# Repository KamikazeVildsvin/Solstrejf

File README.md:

# Solstrejf - 4 Voice Sine Wave Drone Oscillator
This repository contains the simulation, schematic ,and PCB files for **Solstrejf**.
Some custom KiCad footprints, 3D models, and symbols are used in this project. 
This is included as a git submodule, which means that if you want to work with the KiCad projects in this repo, it should be cloned with the `--recursive` option like so: 

```
git clone --recursive "https://github.com/KamikazeVildsvin/Solstrejf.git"
```

### Introduction & Overview
Solstrejf, roughly translated from Danish to "sun streak" or "sun touch", is a four-voice analog sine wave drone oscillator. 
I was on a hike in Sweden out near a beautiful forest lake just around the break of dawn. 
The way the sun interacted with nature gave me a real sense of calm and ease. 
At that moment I thought, what if I could create an instrument that would be able to replicate this feeling? 
A sine wave drone synthesizer came to my mind, similar to the early Musique Concrète test equipment techniques.

###### Block Diagram

I wanted the instrument to be playful and interactive. 
Four sine wave oscillators in itself are maybe not that interesting and can become static. 
A modulation matrix, which would allow for all four voices to modulate parameters like frequency and amplitude on all other voices would create more complex soundscapes. 
The basic idea and block diagram can be seen above, where four identical voice boards are connected to the mod-matrix board and a power supply/mixer board for output summation.

###### Modulation Matrix & Voice Control Interface

The image above is a render of the modulation matrix and four of the voice board control front panels.
This is essentially user interface of the synthesizer.

## PCB's - KiCad Projects
As indicated by the block diagram above, Solstrejf is broken into four different sub-blocks and PCB's:

- A Power Supply Unit (PSU) & Mixer PCB
- A Modulation Matrix PCB
- A Voice board PCB (x4)
- A Voice board Front Panel PCB (x4)

Each of these PCB's have their own KiCad project with an associated schematic. 
The [`schematics`](schematics) directory contains some of the latest prints of the different schematics. 
The revision may not match with the KiCad files, so be sure to double check the actual KiCad project files to be certain.

#### Interactive BOM
All of the four PCB's have an interactive BOM which is generated using the [InteractiveHtmlBom](https://github.com/openscopeproject/InteractiveHtmlBom) KiCad plugin.
The interactive bom allows to see where the components should be placed on the board and also have a checklist build in, which makes it much easier to assemble the PCB's.
You can also export the BOM to a CSV or TXT file for a more traditional BOM.

### PSU / Audio Mixer
Use to generate the +/-15V supply and sum all of the left and right audio channels of the four voices.

[KiCad Project Files](pcb/solstrejf-PSU-mixer/)

[Link to interactive BOM](https://html-preview.github.io/?url=https://github.com/KamikazeVildsvin/Solstrejf/blob/master/pcb/solstrejf-PSU-mixer/bom/ibom.html)

###### PCB

###### 3D Model : Top View

###### 3D Model : Side View

### Mod-Matrix
Connects to each of the four voice boards to route the modulation from and to each of the voices.
Each voice can modulate the amplitude, frequency and pan of all other voices.

[KiCad Project Files](pcb/solstrejf-modmatrix-pots)

[Link to interactive BOM](https://html-preview.github.io/?url=https://github.com/KamikazeVildsvin/Solstrejf/blob/master/pcb/solstrejf-modmatrix-pots/bom/ibom.html)

###### PCB 

###### 3D Model : Front-Side

###### 3D Model : Back-Side 

### Voice board 
The voice board is the actual sine wave oscillator and control voltage board.
Solstrejf consists of four of these voice boards.

[KiCad Project Files](pcb/solstrejf-voiceboard-core/)

[Link to interactive BOM](https://html-preview.github.io/?url=https://github.com/KamikazeVildsvin/Solstrejf/blob/master/pcb/solstrejf-voiceboard-core/bom/ibom.html)

###### PCB

###### 3D Model : Top View

###### 3D Model : Side View

### Voice board Front Panel
The voice board needs a control interface for the base pan, frequency, and volume. All of the potentiometers that control the voice board are located on this front panel for easier assembling. 

[KiCad Project Files](pcb/solstrejf-voiceboard-frontpanel/)

[Link to interactive BOM](https://html-preview.github.io/?url=https://github.com/KamikazeVildsvin/Solstrejf/blob/master/pcb/solstrejf-voiceboard-frontpanel/bom/ibom.html)

###### PCB 

###### 3D Model : Front Side

###### 3D Model : Back Side 

# Prototype Sponsorship - PCBWay
[PCBway](https://www.pcbway.com/) was so kind to reach out and offer to sponsor the first batch of all four PCBs for Solstrejf!
Essentially, they paid for the production of 5x of each of the four PCBs, which was a great help to reduce the cost of this project.

It was very easy to order from PCBWay using the [PCBWay KiCad Export Plugin](https://github.com/pcbway/PCBWay-Plug-in-for-Kicad).
With one click, all of the needed Gerber and drill files were created and packaged in a neat zip file that could be uploaded directly to PCBWay's website for ordering.

I'm very satisfied with the build quality of the PCBs that I have received for my first prototype of Solstrejf.
The silkscreen and edge cuts were very smooth and pleasant to look at, which especially is nice for the modulation matrix and the voice board front panels (since the user has to look at these PCBs).

Thanks to PCBWay for sponsoring the prototype PCBs.

*pictures coming soon...*

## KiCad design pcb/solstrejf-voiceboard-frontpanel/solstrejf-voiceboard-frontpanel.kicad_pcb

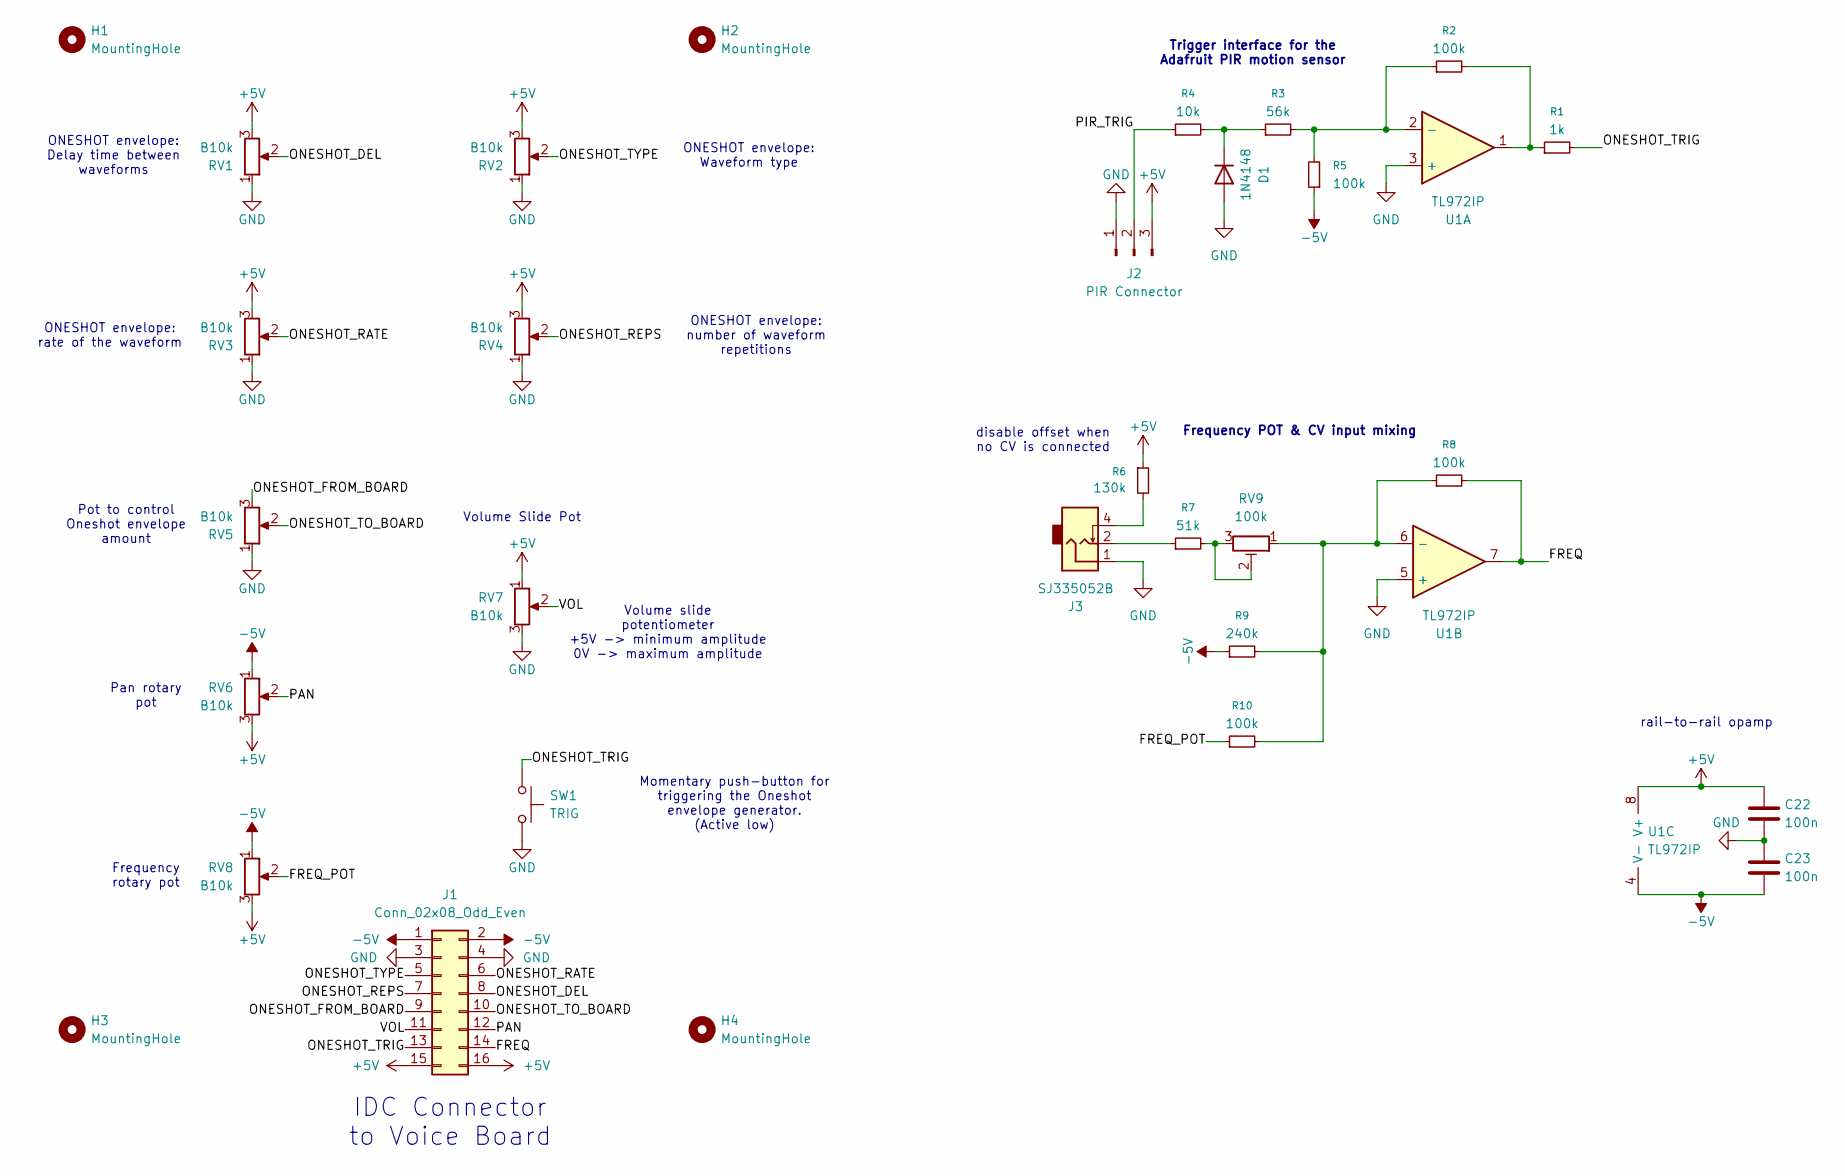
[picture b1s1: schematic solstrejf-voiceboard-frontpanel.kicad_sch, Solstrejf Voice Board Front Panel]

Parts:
C22, C23: 100n; C_Disc_D5.0mm_W2.5mm_P5.00mm
D1: 1N4148; D_DO-35_SOD27_P7.62mm_Horizontal
H1, H2, H3, H4: MountingHole; MountingHole_3.2mm_M3_DIN965
J1: Conn_02x08_Odd_Even; IDC-Header_2x08_P2.54mm_Vertical
J2: PIR Connector; PinHeader_1x03_P2.54mm_Vertical
J3: SJ335052B
R1: 1k; R_Axial_DIN0207_L6.3mm_D2.5mm_P10.16mm_Horizontal
R2, R5, R8, R10: 100k; R_Axial_DIN0207_L6.3mm_D2.5mm_P10.16mm_Horizontal
R3: 56k; R_Axial_DIN0207_L6.3mm_D2.5mm_P10.16mm_Horizontal
R4: 10k; R_Axial_DIN0207_L6.3mm_D2.5mm_P10.16mm_Horizontal
R6: 130k; R_Axial_DIN0207_L6.3mm_D2.5mm_P10.16mm_Horizontal
R7: 51k; R_Axial_DIN0207_L6.3mm_D2.5mm_P10.16mm_Horizontal
R9: 240k; R_Axial_DIN0207_L6.3mm_D2.5mm_P10.16mm_Horizontal
RV1, RV2, RV3, RV4, RV5, RV6, RV8: B10k; Potentiometer_Alpha_RD901F-40-00D_Single_Vertical
RV7: B10k; Potentiometer_Alpha_slide_pot_30mm
RV9: 100k; Potentiometer_Bourns_3296Y_Vertical
SW1: TRIG; SW_SPST_Omron_B3F-40xx
U1: TL972IP; DIP-8_W7.62mm_Socket

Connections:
+5V: C22.1, J1.15, J1.16, J2.3, R6.1, RV1.3, RV2.3, RV3.3, RV4.3, RV6.3, RV7.1, RV8.3, U1.8 (V+)
-5V: C23.2, J1.1, J1.2, R5.1, R9.1, RV6.1, RV8.1, U1.4 (V-)
/FREQ: J1.14, R8.2, U1.7
/FREQ_POT: R10.1, RV8.2
/ONESHOT_DEL: J1.8, RV1.2
/ONESHOT_FROM_BOARD: J1.9, RV5.3
/ONESHOT_RATE: J1.6, RV3.2
/ONESHOT_REPS: J1.7, RV4.2
/ONESHOT_TO_BOARD: J1.10, RV5.2
/ONESHOT_TRIG: J1.13, R1.2, SW1.1
/ONESHOT_TYPE: J1.5, RV2.2
/PAN: J1.12, RV6.2
/PIR_TRIG: J2.2, R4.1
/VOL: J1.11, RV7.2
GND: C22.2, C23.1, D1.2 (A), J1.3, J1.4, J2.1, J3.1, RV1.1, RV2.1, RV3.1, RV4.1, RV5.1, RV7.3, SW1.2, U1.3 (+), U1.5 (+)
unnamed: D1.1 (K), R3.1, R4.2
unnamed: J3.2, R7.1
unnamed: J3.4, R6.2
unnamed: R1.1, R2.2, U1.1
unnamed: R7.2, RV9.2, RV9.3
unnamed: R2.1, R3.2, R5.2, U1.2 (-)
unnamed: R8.1, R9.2, R10.2, RV9.1, U1.6 (-)

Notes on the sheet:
Pan rotary pot
Trigger interface for the Adafruit PIR motion sensor
ONESHOT envelope: rate of the waveform
disable offset when no CV is connected
Frequency rotary pot
Frequency POT & CV input mixing
Volume slide potentiometer +5V -> minimum amplitude 0V -> maximum amplitude
ONESHOT envelope: number of waveform repetitions
rail-to-rail opamp
IDC Connector to Voice Board
ONESHOT envelope: Waveform type
ONESHOT envelope: Delay time between waveforms
Volume Slide Pot
Pot to control Oneshot envelope amount
Momentary push-button for triggering the Oneshot envelope generator. (Active low)

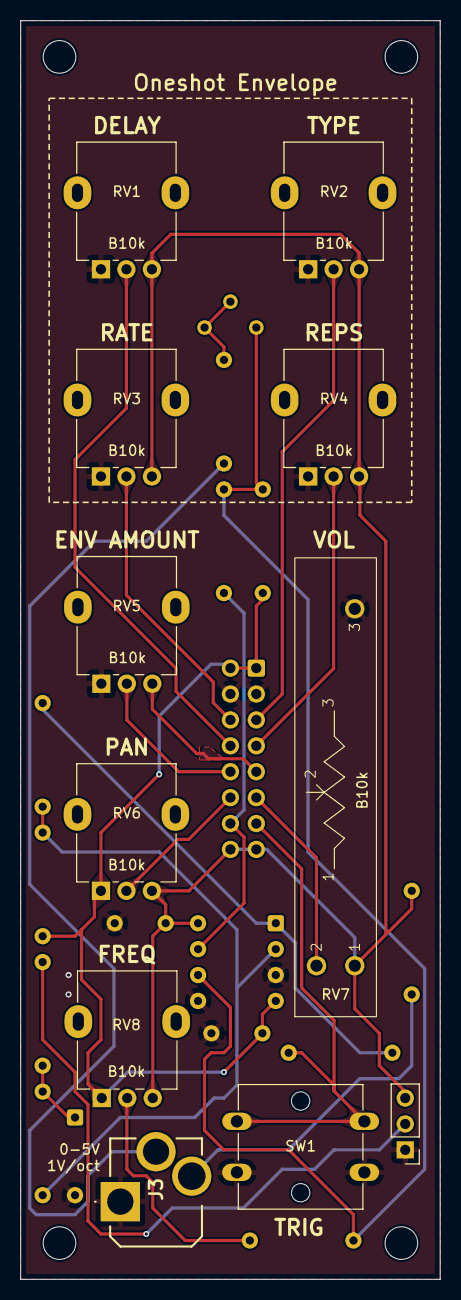
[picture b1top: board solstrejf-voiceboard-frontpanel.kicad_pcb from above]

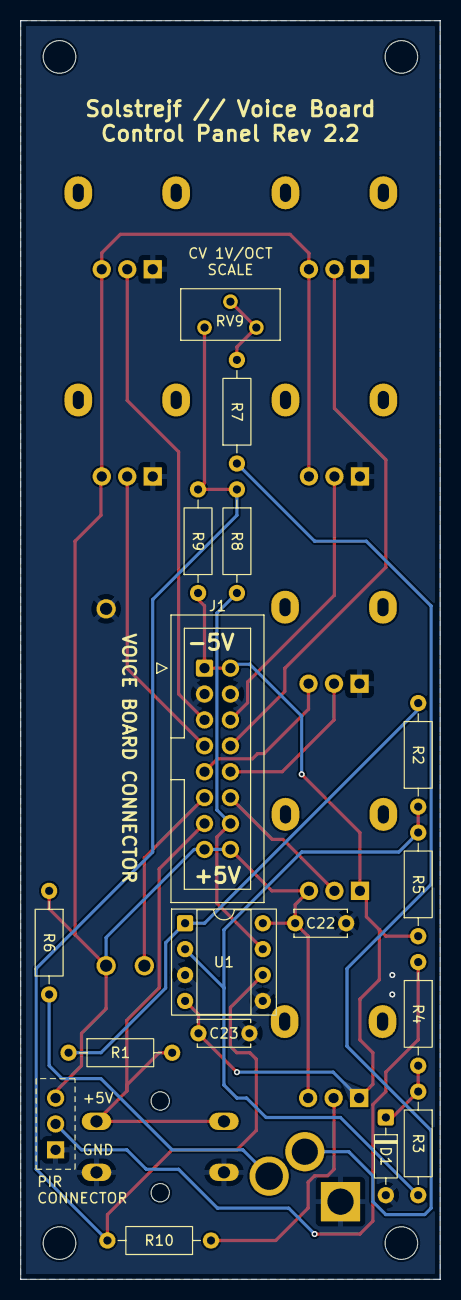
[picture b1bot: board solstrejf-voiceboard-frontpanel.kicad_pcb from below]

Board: 2 copper layers, 41.1 x 123.4 mm, 31 parts (16 on the bottom side), 22 nets.

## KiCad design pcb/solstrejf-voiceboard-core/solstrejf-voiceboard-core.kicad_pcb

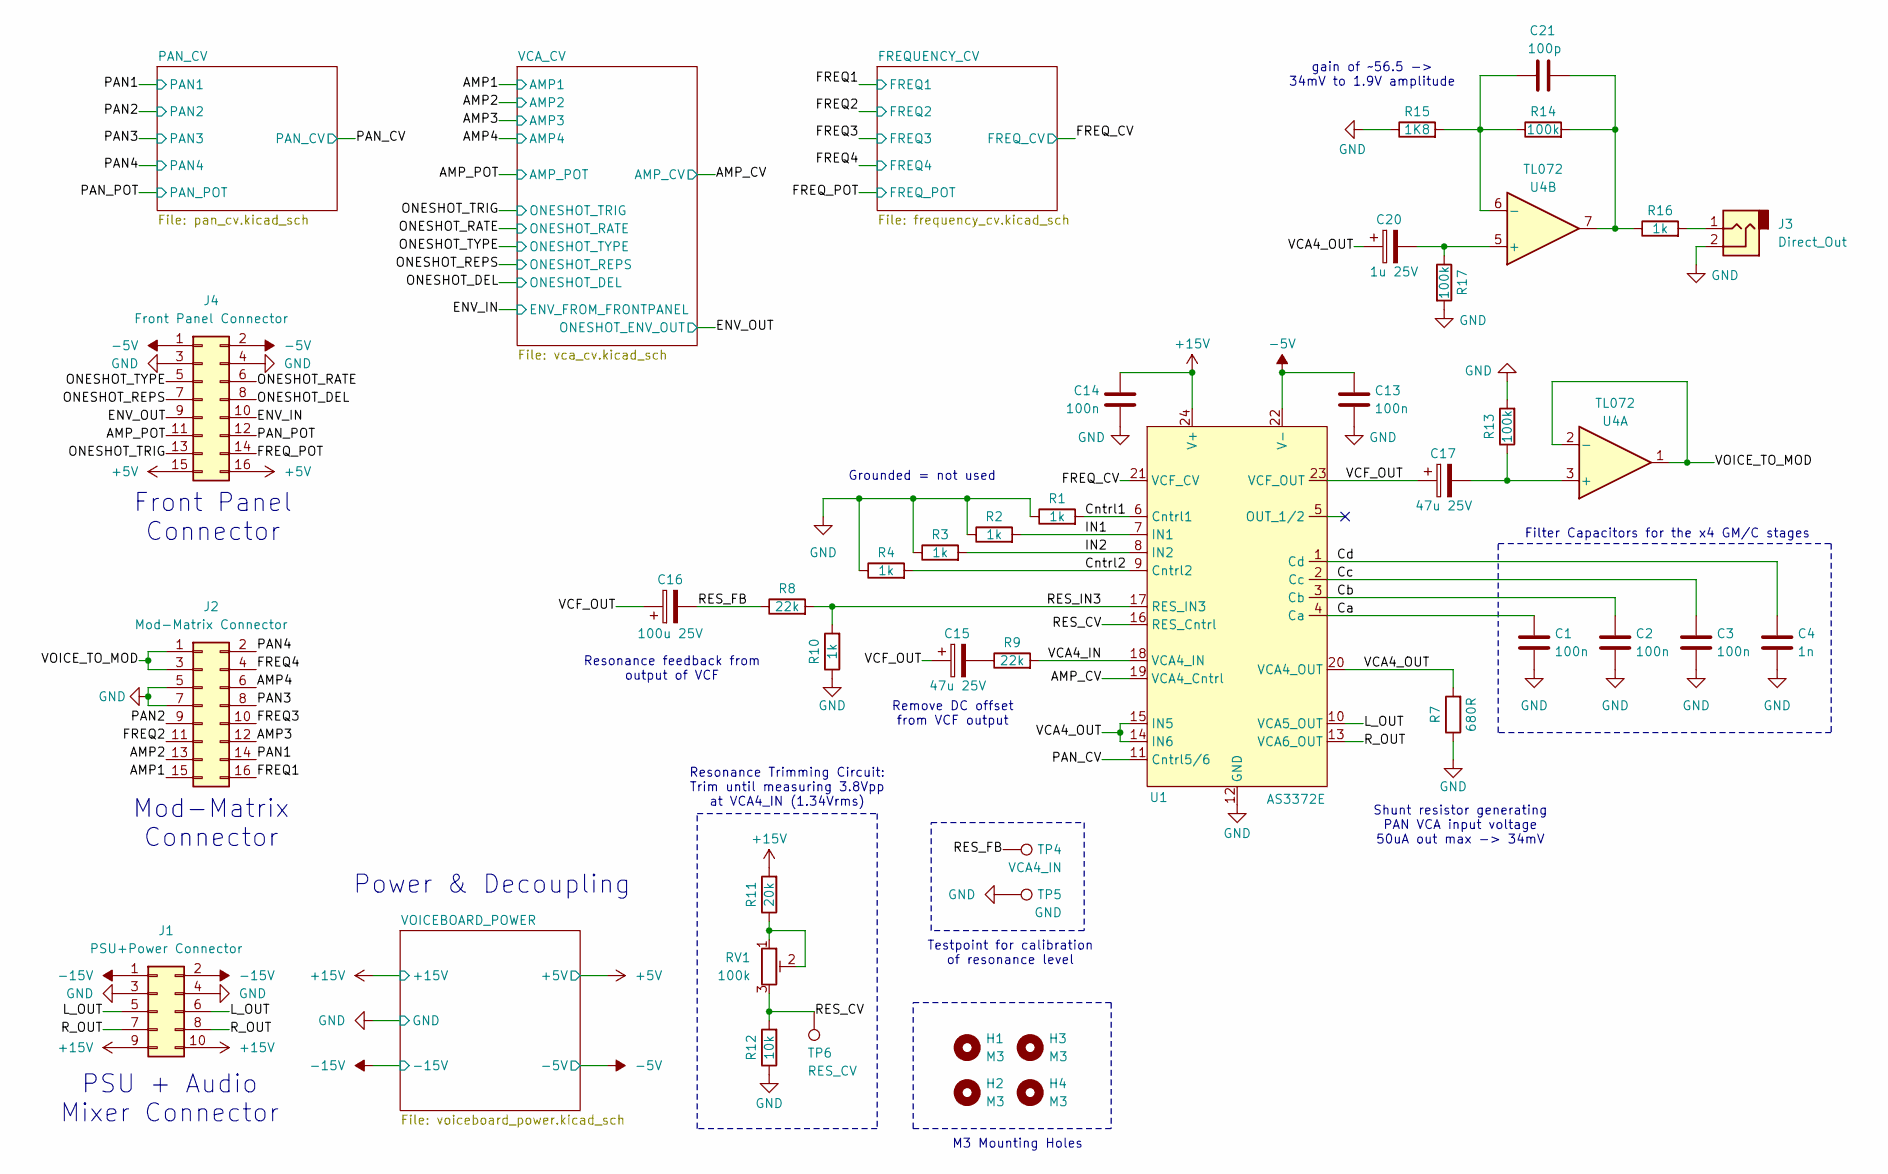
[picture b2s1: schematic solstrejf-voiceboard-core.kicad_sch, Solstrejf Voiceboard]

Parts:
C1, C2, C3, C13, C14: 100n; C_Disc_D5.0mm_W2.5mm_P5.00mm
C4: 1n; C_Disc_D5.0mm_W2.5mm_P5.00mm
C15, C17: 47u 25V; CP_Radial_D5.0mm_P2.50mm
C16: 100u 25V; CP_Radial_D6.3mm_P2.50mm
C20: 1u 25V; CP_Radial_D5.0mm_P2.50mm
C21: 100p; C_Disc_D5.0mm_W2.5mm_P5.00mm
H1, H2, H3, H4: M3; MountingHole_3.2mm_M3_DIN965
J1: PSU+Power Connector; IDC-Header_2x05_P2.54mm_Vertical
J2: Mod-Matrix Connector; IDC-Header_2x08_P2.54mm_Vertical
J3: Direct_Out; PinHeader_1x02_P2.54mm_Vertical
J4: Front Panel Connector; IDC-Header_2x08_P2.54mm_Vertical
R1, R2, R3, R4, R10, R16: 1k; R_Axial_DIN0207_L6.3mm_D2.5mm_P10.16mm_Horizontal
R7: 680R; R_Axial_DIN0207_L6.3mm_D2.5mm_P10.16mm_Horizontal
R8, R9: 22k; R_Axial_DIN0207_L6.3mm_D2.5mm_P10.16mm_Horizontal
R11: 20k; R_Axial_DIN0207_L6.3mm_D2.5mm_P10.16mm_Horizontal
R12: 10k; R_Axial_DIN0207_L6.3mm_D2.5mm_P10.16mm_Horizontal
R13, R14, R17: 100k; R_Axial_DIN0207_L6.3mm_D2.5mm_P10.16mm_Horizontal
R15: 1K8; R_Axial_DIN0207_L6.3mm_D2.5mm_P10.16mm_Horizontal
RV1: 100k; Potentiometer_Bourns_3296Y_Vertical
TP4: VCA4_IN; TestPoint_Loop_D2.50mm_Drill1.0mm
TP5: GND; TestPoint_Loop_D2.50mm_Drill1.0mm
TP6: RES_CV; TestPoint_Loop_D2.50mm_Drill1.0mm
U1: AS3372E; DIP-24_W7.62mm_Socket
U4: TL072; DIP-8_W7.62mm_Socket

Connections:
+5V: J4.15, J4.16; also elsewhere on the board
+15V: C14.1, J1.9, J1.10, R11.2, U1.24 (V+); also elsewhere on the board
-5V: C13.1, J4.1, J4.2, U1.22 (V-); also elsewhere on the board
-15V: J1.1, J1.2; also elsewhere on the board
/AMP1: J2.15; also elsewhere on the board
/AMP2: J2.13; also elsewhere on the board
/AMP3: J2.12; also elsewhere on the board
/AMP4: J2.6; also elsewhere on the board
/AMP_CV: U1.19 (VCA4_Cntrl); also elsewhere on the board
/AMP_POT: J4.11; also elsewhere on the board
/Ca: C1.1, U1.4 (Ca)
/Cb: C2.1, U1.3 (Cb)
/Cc: C3.1, U1.2 (Cc)
/Cd: C4.1, U1.1 (Cd)
/Cntrl1: R1.2, U1.6 (Cntrl1)
/Cntrl2: R4.2, U1.9 (Cntrl2)
/ENV_IN: J4.10; also elsewhere on the board
/ENV_OUT: J4.9; also elsewhere on the board
/FREQ1: J2.16; also elsewhere on the board
/FREQ2: J2.11; also elsewhere on the board
/FREQ3: J2.10; also elsewhere on the board
/FREQ4: J2.4; also elsewhere on the board
/FREQ_CV: U1.21 (VCF_CV); also elsewhere on the board
/FREQ_POT: J4.14; also elsewhere on the board
/IN1: R2.2, U1.7 (IN1)
/IN2: R3.2, U1.8 (IN2)
/L_OUT: J1.5, J1.6, U1.10 (VCA5_OUT)
/ONESHOT_DEL: J4.8; also elsewhere on the board
/ONESHOT_RATE: J4.6; also elsewhere on the board
/ONESHOT_REPS: J4.7; also elsewhere on the board
/ONESHOT_TRIG: J4.13; also elsewhere on the board
/ONESHOT_TYPE: J4.5; also elsewhere on the board
/PAN1: J2.14; also elsewhere on the board
/PAN2: J2.9; also elsewhere on the board
/PAN3: J2.8; also elsewhere on the board
/PAN4: J2.2; also elsewhere on the board
/PAN_CV: U1.11 (Cntrl5/6); also elsewhere on the board
/PAN_POT: J4.12; also elsewhere on the board
/RES_CV: R12.2, RV1.3, TP6.1, U1.16 (RES_Cntrl)
/RES_FB: C16.2, R8.1, TP4.1
/RES_IN3: R8.2, R10.2, U1.17 (RES_IN3)
/R_OUT: J1.7, J1.8, U1.13 (VCA6_OUT)
/VCA4_IN: R9.2, U1.18 (VCA4_IN)
/VCA4_OUT: C20.1, R7.2, U1.14 (IN6), U1.15 (IN5), U1.20 (VCA4_OUT)
/VCF_OUT: C15.1, C16.1, C17.1, U1.23 (VCF_OUT)
/VOICE_TO_MOD: J2.1, J2.3, U4.1, U4.2 (-)
GND: C1.2, C2.2, C3.2, C4.2, C13.2, C14.2, J1.3, J1.4, J2.5, J2.7, J3.2, J4.3, J4.4, R1.1, R2.1, R3.1, R4.1, R7.1, R10.1, R12.1, R13.2, R15.1, R17.2, TP5.1, U1.12 (GND); also elsewhere on the board
unnamed: C15.2, R9.1
unnamed: C21.2, R14.2, R16.1, U4.7
unnamed: J3.1, R16.2
unnamed: R11.1, RV1.1, RV1.2
unnamed: C17.2, R13.1, U4.3 (+)
unnamed: C20.2, R17.1, U4.5 (+)
unnamed: C21.1, R14.1, R15.2, U4.6 (-)

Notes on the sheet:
Resonance feedback from output of VCF
Shunt resistor generating PAN VCA input voltage 50uA out max -> 34mV
M3 Mounting Holes
Grounded = not used
gain of ~56.5 -> 34mV to 1.9V amplitude
Mod-Matrix Connector
Front Panel Connector
PSU + Audio Mixer Connector
Power & Decoupling
Remove DC offset from VCF output
Testpoint for calibration of resonance level
Filter Capacitors for the x4 GM/C stages
Resonance Trimming Circuit: Trim until measuring 3.8Vpp at VCA4_IN (1.34Vrms)

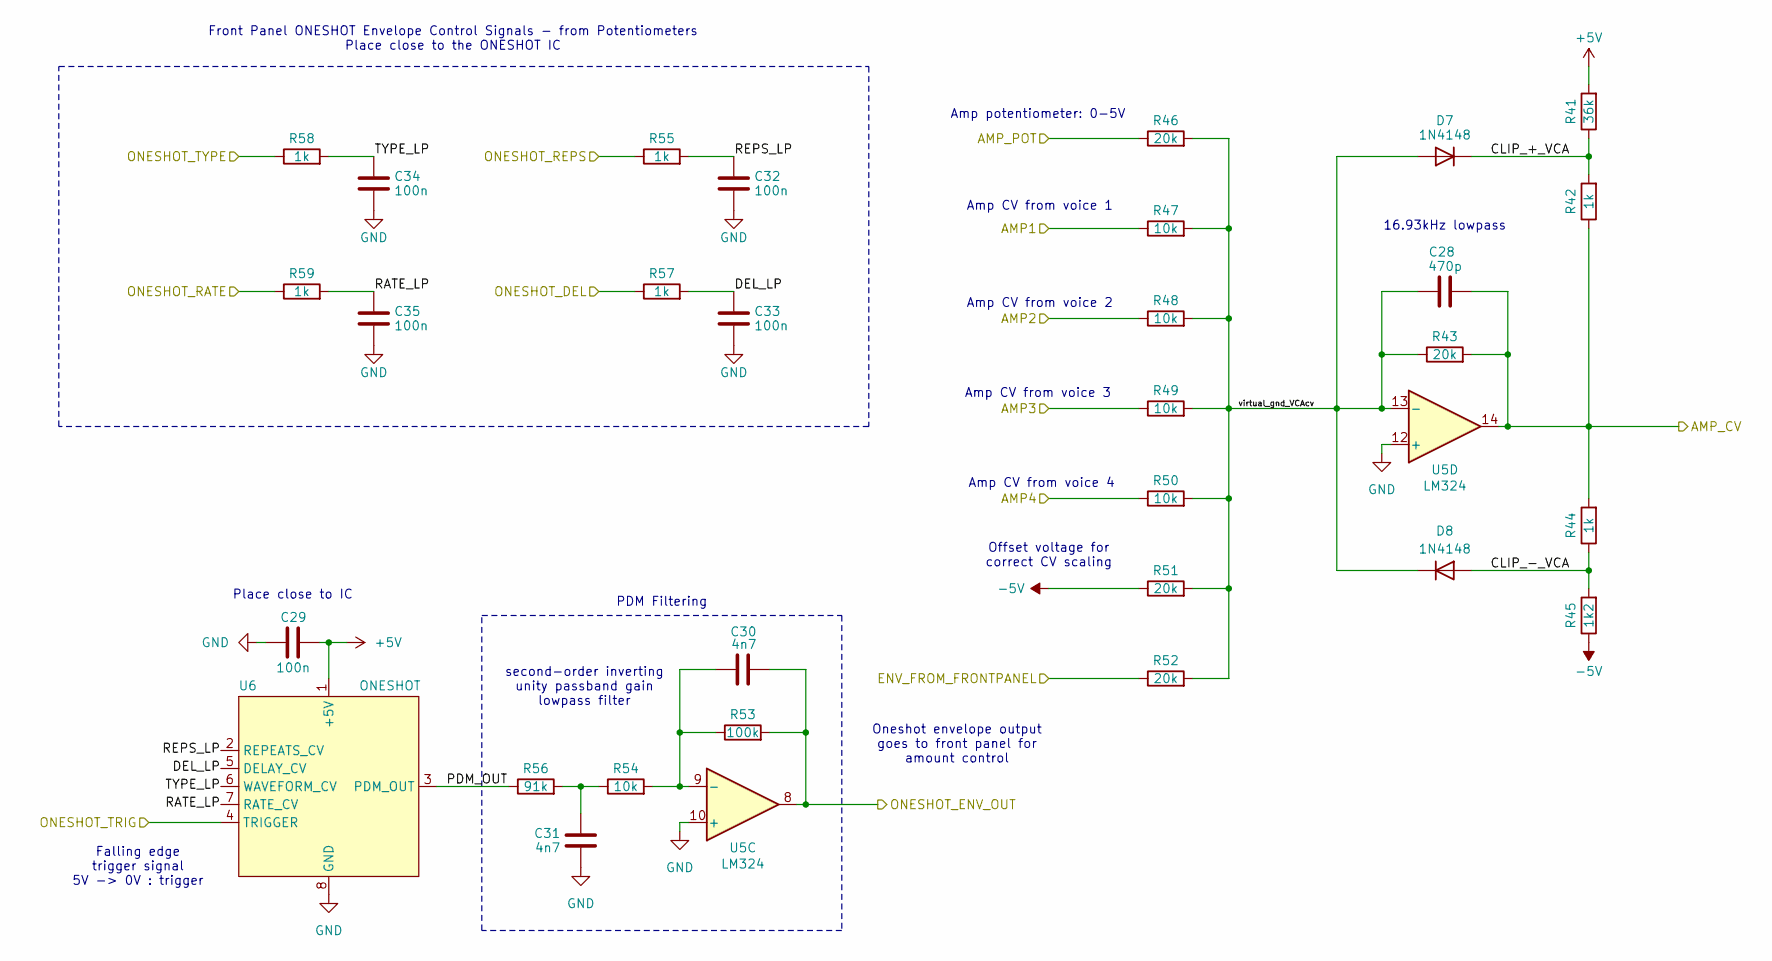
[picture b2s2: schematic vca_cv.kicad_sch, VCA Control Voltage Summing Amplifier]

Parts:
C28: 470p; C_Disc_D5.0mm_W2.5mm_P5.00mm
C29, C32, C33, C34, C35: 100n; C_Disc_D5.0mm_W2.5mm_P5.00mm
C30, C31: 4n7; C_Disc_D5.0mm_W2.5mm_P5.00mm
D7, D8: 1N4148; D_DO-35_SOD27_P7.62mm_Horizontal
R41: 36k; R_Axial_DIN0207_L6.3mm_D2.5mm_P10.16mm_Horizontal
R42, R44, R55, R57, R58, R59: 1k; R_Axial_DIN0207_L6.3mm_D2.5mm_P10.16mm_Horizontal
R43, R46, R51, R52: 20k; R_Axial_DIN0207_L6.3mm_D2.5mm_P10.16mm_Horizontal
R45: 1k2; R_Axial_DIN0207_L6.3mm_D2.5mm_P10.16mm_Horizontal
R47, R48, R49, R50, R54: 10k; R_Axial_DIN0207_L6.3mm_D2.5mm_P10.16mm_Horizontal
R53: 100k; R_Axial_DIN0207_L6.3mm_D2.5mm_P10.16mm_Horizontal
R56: 91k; R_Axial_DIN0207_L6.3mm_D2.5mm_P10.16mm_Horizontal
U5: LM324; DIP-14_W7.62mm
U6: ONESHOT; DIP-8_W7.62mm_Socket

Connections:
+5V: C29.2, R41.2, U6.1 (+5V); also elsewhere on the board
-5V: R45.1, R51.1; also elsewhere on the board
/AMP1: R47.1; also elsewhere on the board
/AMP2: R48.1; also elsewhere on the board
/AMP3: R49.1; also elsewhere on the board
/AMP4: R50.1; also elsewhere on the board
/AMP_CV: C28.2, R42.1, R43.2, R44.2, U5.14; also elsewhere on the board
/AMP_POT: R46.1; also elsewhere on the board
/ENV_IN: R52.1; also elsewhere on the board
/ENV_OUT: C30.2, R53.2, U5.8; also elsewhere on the board
/ONESHOT_DEL: R57.1; also elsewhere on the board
/ONESHOT_RATE: R59.1; also elsewhere on the board
/ONESHOT_REPS: R55.1; also elsewhere on the board
/ONESHOT_TRIG: U6.4 (TRIGGER); also elsewhere on the board
/ONESHOT_TYPE: R58.1; also elsewhere on the board
/VCA_CV/CLIP_+_VCA: D7.1 (K), R41.1, R42.2
/VCA_CV/CLIP_-_VCA: D8.2 (A), R44.1, R45.2
/VCA_CV/DEL_LP: C33.2, R57.2, U6.5 (DELAY_CV)
/VCA_CV/PDM_OUT: R56.1, U6.3 (PDM_OUT)
/VCA_CV/RATE_LP: C35.2, R59.2, U6.7 (RATE_CV)
/VCA_CV/REPS_LP: C32.2, R55.2, U6.2 (REPEATS_CV)
/VCA_CV/TYPE_LP: C34.2, R58.2, U6.6 (WAVEFORM_CV)
/VCA_CV/virtual_gnd_VCAcv: C28.1, D7.2 (A), D8.1 (K), R43.1, R46.2, R47.2, R48.2, R49.2, R50.2, R51.2, R52.2, U5.13 (-)
GND: C29.1, C31.1, C32.1, C33.1, C34.1, C35.1, U5.10 (+), U5.12 (+), U6.8 (GND); also elsewhere on the board
unnamed: C31.2, R54.1, R56.2
unnamed: C30.1, R53.1, R54.2, U5.9 (-)

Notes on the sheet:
Amp CV from voice 1
Offset voltage for correct CV scaling
Oneshot envelope output goes to front panel for amount control
Amp CV from voice 2
PDM Filtering
Place close to IC
Amp potentiometer: 0-5V
Falling edge trigger signal 5V -> 0V : trigger
16.93kHz lowpass
second-order inverting unity passband gain lowpass filter
Front Panel ONESHOT Envelope Control Signals - from Potentiometers Place close to the ONESHOT IC
Amp CV from voice 3
Amp CV from voice 4

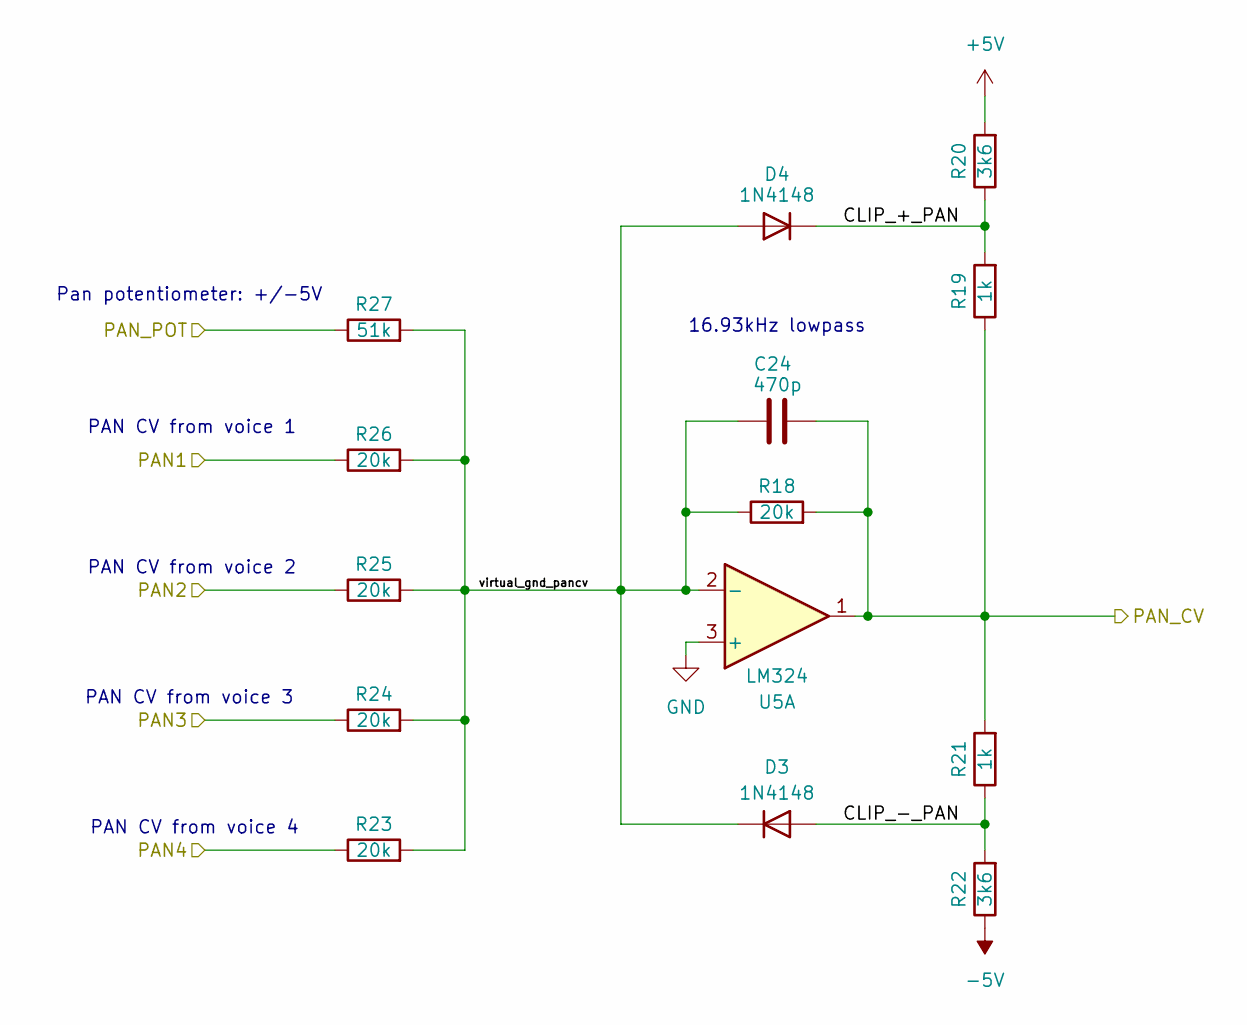
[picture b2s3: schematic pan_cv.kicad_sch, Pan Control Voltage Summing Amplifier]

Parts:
C24: 470p; C_Disc_D5.0mm_W2.5mm_P5.00mm
D3, D4: 1N4148; D_DO-35_SOD27_P7.62mm_Horizontal
R18, R23, R24, R25, R26: 20k; R_Axial_DIN0207_L6.3mm_D2.5mm_P10.16mm_Horizontal
R19, R21: 1k; R_Axial_DIN0207_L6.3mm_D2.5mm_P10.16mm_Horizontal
R20, R22: 3k6; R_Axial_DIN0207_L6.3mm_D2.5mm_P10.16mm_Horizontal
R27: 51k; R_Axial_DIN0207_L6.3mm_D2.5mm_P10.16mm_Horizontal
U5: LM324; DIP-14_W7.62mm

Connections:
+5V: R20.2; also elsewhere on the board
-5V: R22.1; also elsewhere on the board
/PAN1: R26.1; also elsewhere on the board
/PAN2: R25.1; also elsewhere on the board
/PAN3: R24.1; also elsewhere on the board
/PAN4: R23.1; also elsewhere on the board
/PAN_CV: C24.2, R18.2, R19.1, R21.2, U5.1; also elsewhere on the board
/PAN_CV/CLIP_+_PAN: D4.1 (K), R19.2, R20.1
/PAN_CV/CLIP_-_PAN: D3.2 (A), R21.1, R22.2
/PAN_CV/virtual_gnd_pancv: C24.1, D3.1 (K), D4.2 (A), R18.1, R23.2, R24.2, R25.2, R26.2, R27.2, U5.2 (-)
/PAN_POT: R27.1; also elsewhere on the board
GND: U5.3 (+); also elsewhere on the board

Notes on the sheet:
PAN CV from voice 3
PAN CV from voice 1
Pan potentiometer: +/-5V
16.93kHz lowpass
PAN CV from voice 2
PAN CV from voice 4

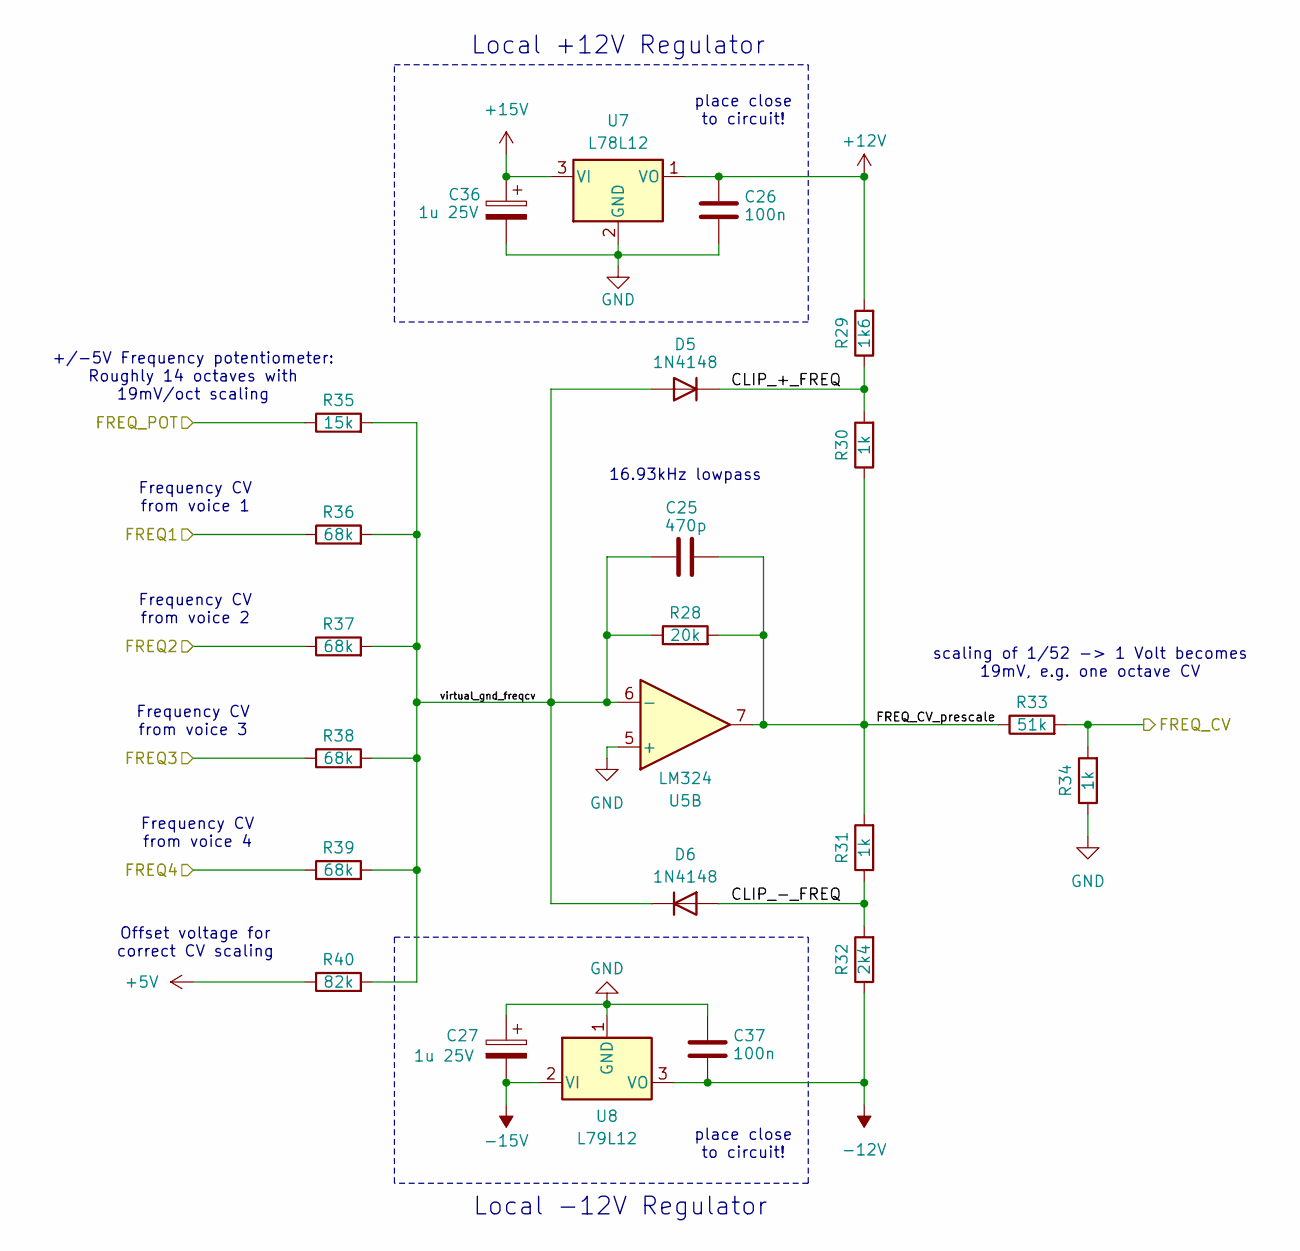
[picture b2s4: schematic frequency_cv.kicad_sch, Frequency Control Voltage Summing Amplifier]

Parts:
C25: 470p; C_Disc_D5.0mm_W2.5mm_P5.00mm
C26, C37: 100n; C_Disc_D5.0mm_W2.5mm_P5.00mm
C27, C36: 1u 25V; CP_Radial_D5.0mm_P2.50mm
D5, D6: 1N4148; D_DO-35_SOD27_P7.62mm_Horizontal
R28: 20k; R_Axial_DIN0207_L6.3mm_D2.5mm_P10.16mm_Horizontal
R29: 1k6; R_Axial_DIN0207_L6.3mm_D2.5mm_P10.16mm_Horizontal
R30, R31, R34: 1k; R_Axial_DIN0207_L6.3mm_D2.5mm_P10.16mm_Horizontal
R32: 2k4; R_Axial_DIN0207_L6.3mm_D2.5mm_P10.16mm_Horizontal
R33: 51k; R_Axial_DIN0207_L6.3mm_D2.5mm_P10.16mm_Horizontal
R35: 15k; R_Axial_DIN0207_L6.3mm_D2.5mm_P10.16mm_Horizontal
R36, R37, R38, R39: 68k; R_Axial_DIN0207_L6.3mm_D2.5mm_P10.16mm_Horizontal
R40: 82k; R_Axial_DIN0207_L6.3mm_D2.5mm_P10.16mm_Horizontal
U5: LM324; DIP-14_W7.62mm
U7: L78L12; TO-92_Inline
U8: L79L12; TO-92_Inline

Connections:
+5V: R40.1; also elsewhere on the board
+12V: C26.2, R29.2, U7.1 (VO)
+15V: C36.1, U7.3 (VI); also elsewhere on the board
-12V: C37.1, R32.1, U8.3 (VO)
-15V: C27.2, U8.2 (VI); also elsewhere on the board
/FREQ1: R36.1; also elsewhere on the board
/FREQ2: R37.1; also elsewhere on the board
/FREQ3: R38.1; also elsewhere on the board
/FREQ4: R39.1; also elsewhere on the board
/FREQUENCY_CV/CLIP_+_FREQ: D5.1 (K), R29.1, R30.2
/FREQUENCY_CV/CLIP_-_FREQ: D6.2 (A), R31.1, R32.2
/FREQUENCY_CV/FREQ_CV_prescale: C25.2, R28.2, R30.1, R31.2, R33.1, U5.7
/FREQUENCY_CV/virtual_gnd_freqcv: C25.1, D5.2 (A), D6.1 (K), R28.1, R35.2, R36.2, R37.2, R38.2, R39.2, R40.2, U5.6 (-)
/FREQ_CV: R33.2, R34.2; also elsewhere on the board
/FREQ_POT: R35.1; also elsewhere on the board
GND: C26.1, C27.1, C36.2, C37.2, R34.1, U5.5 (+), U7.2 (GND), U8.1 (GND); also elsewhere on the board

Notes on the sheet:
Offset voltage for correct CV scaling
Local +12V Regulator
16.93kHz lowpass
Frequency CV from voice 3
scaling of 1/52 -> 1 Volt becomes 19mV, e.g. one octave CV
Frequency CV from voice 2
Frequency CV from voice 1
place close to circuit!
Frequency CV from voice 4
Local -12V Regulator
+/-5V Frequency potentiometer: Roughly 14 octaves with 19mV/oct scaling

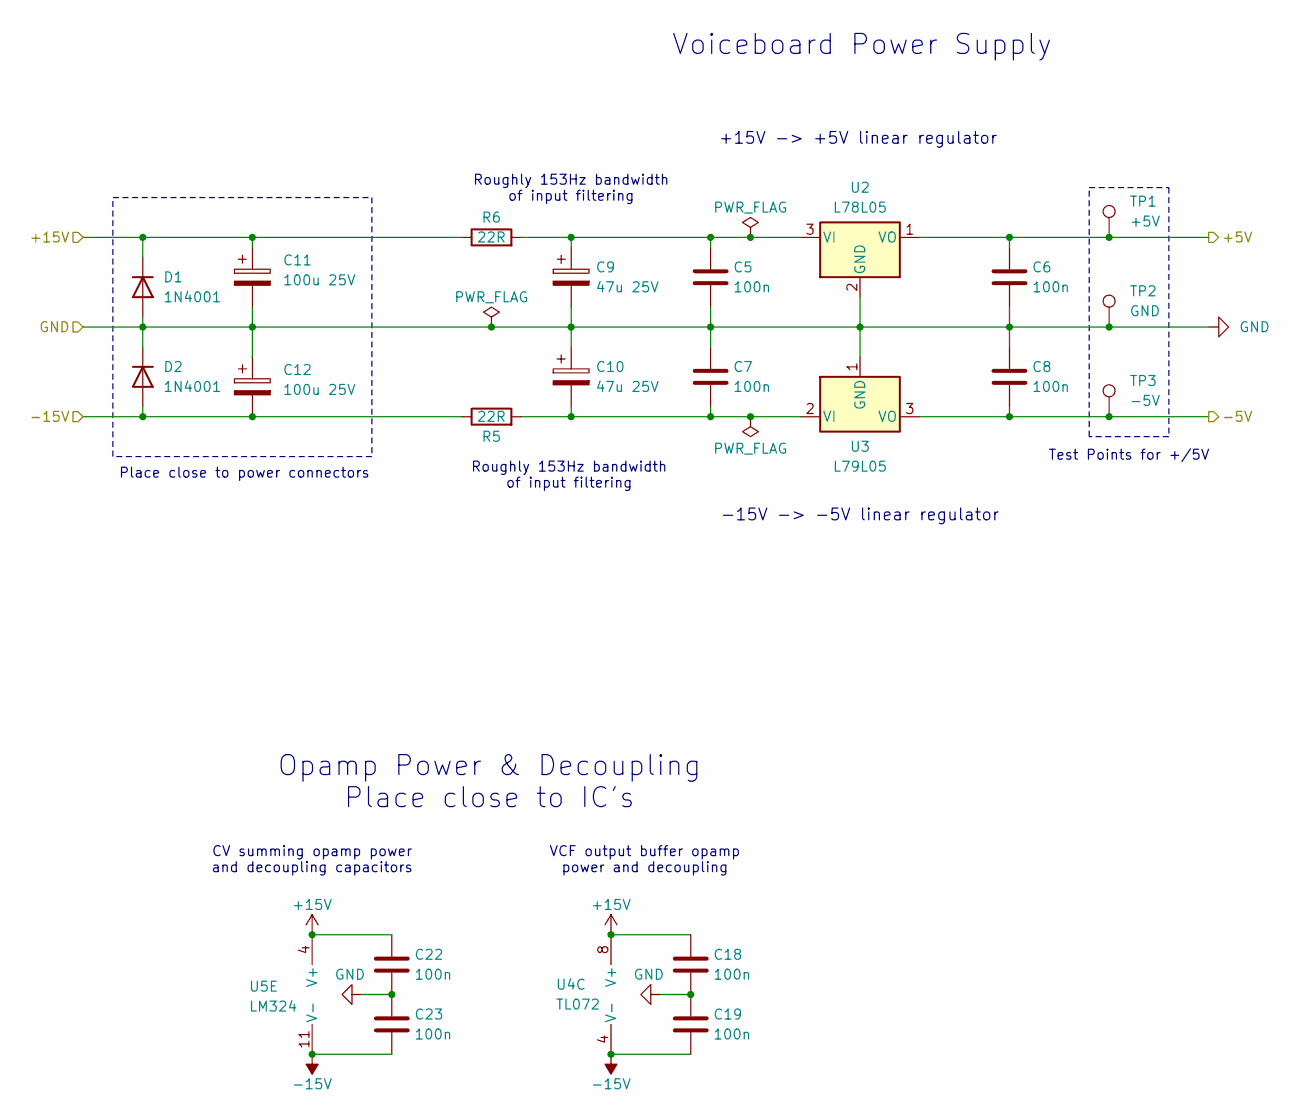
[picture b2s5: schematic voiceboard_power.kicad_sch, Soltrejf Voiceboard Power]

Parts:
C5, C6, C7, C8, C18, C19, C22, C23: 100n; C_Disc_D5.0mm_W2.5mm_P5.00mm
C9, C10: 47u 25V; CP_Radial_D5.0mm_P2.50mm
C11, C12: 100u 25V; CP_Radial_D6.3mm_P2.50mm
D1, D2: 1N4001; D_DO-41_SOD81_P10.16mm_Horizontal
R5, R6: 22R; R_Axial_DIN0207_L6.3mm_D2.5mm_P10.16mm_Horizontal
TP1: +5V; TestPoint_Loop_D2.50mm_Drill1.0mm
TP2: GND; TestPoint_Loop_D2.50mm_Drill1.0mm
TP3: -5V; TestPoint_Loop_D2.50mm_Drill1.0mm
U2: L78L05; TO-92_Inline
U3: L79L05; TO-92_Inline
U4: TL072; DIP-8_W7.62mm_Socket
U5: LM324; DIP-14_W7.62mm

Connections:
+5V: C6.1, TP1.1, U2.1 (VO); also elsewhere on the board
+15V: C11.1, C18.1, C22.1, D1.1 (K), R6.1, U4.8 (V+), U5.4 (V+); also elsewhere on the board
-5V: C8.2, TP3.1, U3.3 (VO); also elsewhere on the board
-15V: C12.2, C19.2, C23.2, D2.2 (A), R5.1, U4.4 (V-), U5.11 (V-); also elsewhere on the board
GND: C5.2, C6.2, C7.1, C8.1, C9.2, C10.1, C11.2, C12.1, C18.2, C19.1, C22.2, C23.1, D1.2 (A), D2.1 (K), TP2.1, U2.2 (GND), U3.1 (GND); also elsewhere on the board
unnamed: C5.1, C9.1, R6.2, U2.3 (VI)
unnamed: C7.2, C10.2, R5.2, U3.2 (VI)

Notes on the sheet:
-15V -> -5V linear regulator
VCF output buffer opamp power and decoupling
+15V -> +5V linear regulator
Opamp Power & Decoupling Place close to IC's
Place close to power connectors
CV summing opamp power and decoupling capacitors
Roughly 153Hz bandwidth of input filtering
Test Points for +/5V
Voiceboard Power Supply

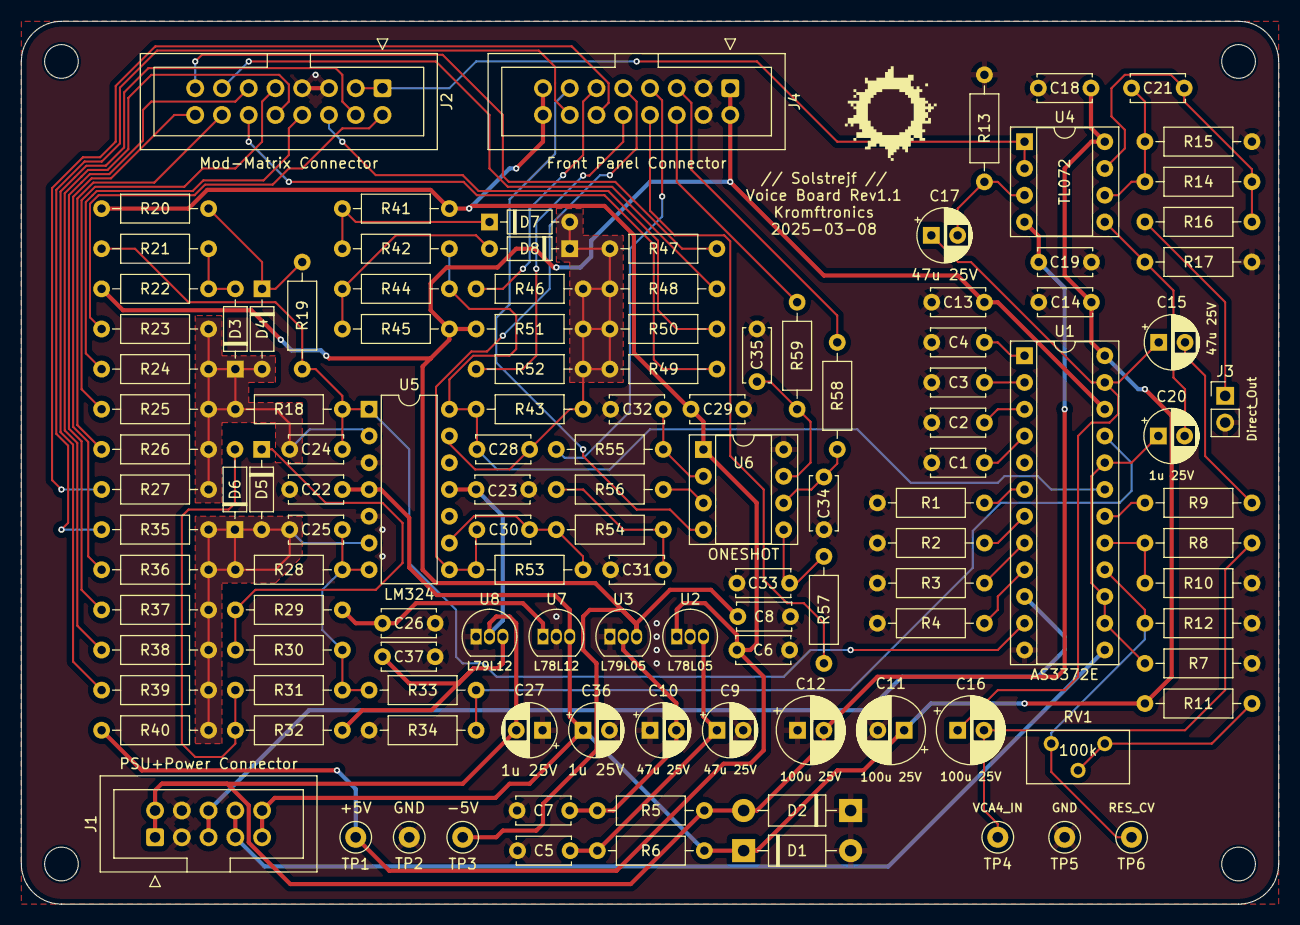
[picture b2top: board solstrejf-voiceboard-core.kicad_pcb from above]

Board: 2 copper layers, 119.4 x 83.8 mm, 127 parts (0 on the bottom side), 75 nets.
